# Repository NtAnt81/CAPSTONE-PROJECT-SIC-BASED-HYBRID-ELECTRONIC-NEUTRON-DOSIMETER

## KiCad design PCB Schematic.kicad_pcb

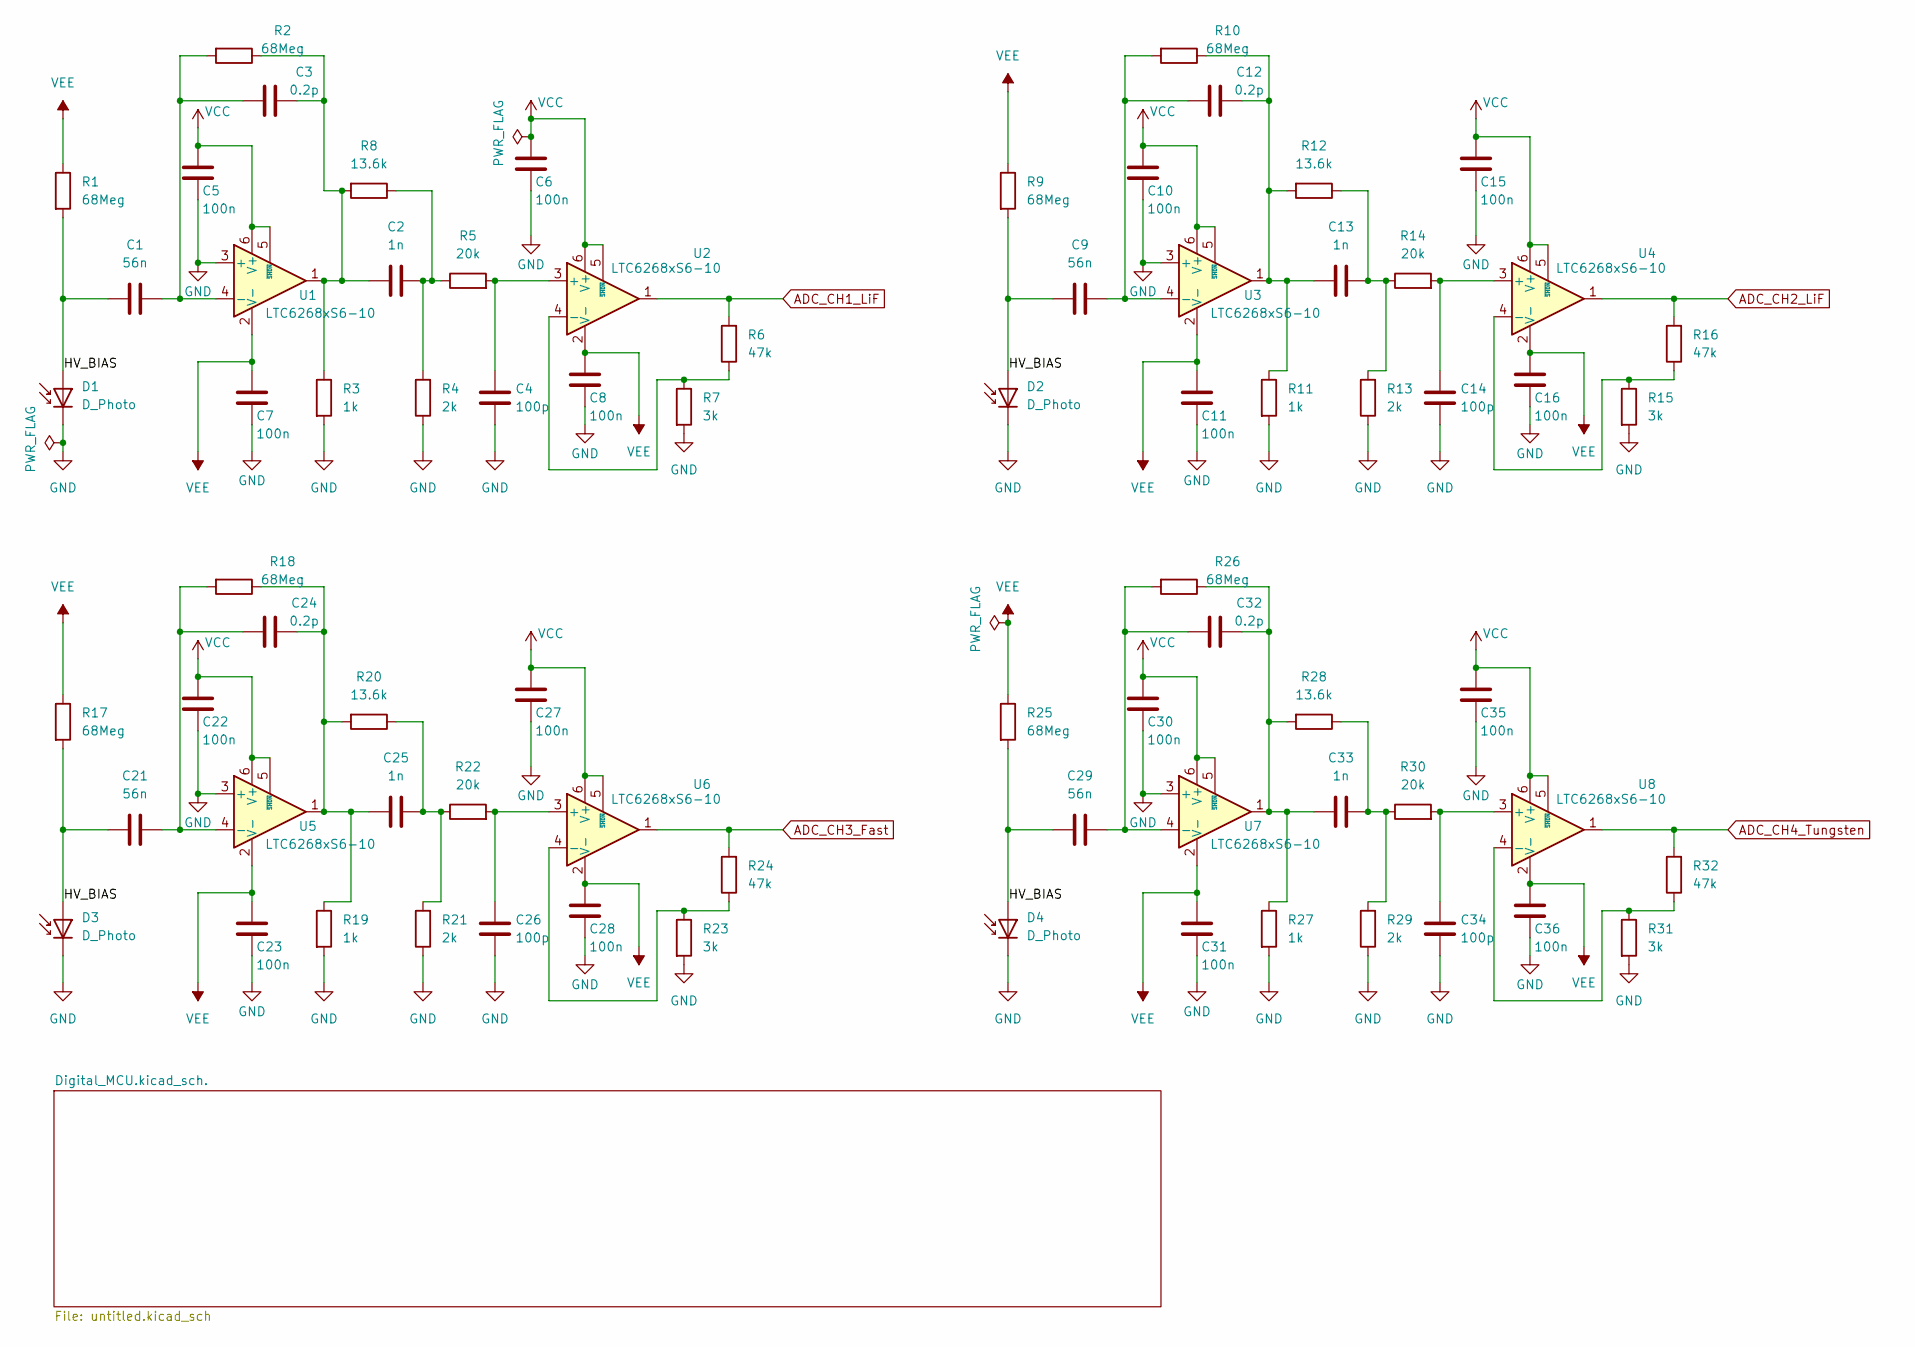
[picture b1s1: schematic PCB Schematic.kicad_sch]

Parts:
C1, C9, C21, C29: 56n; C_0603_1608Metric
C2, C13, C25, C33: 1n; C_0603_1608Metric
C3, C12, C24, C32: 0.2p; C_0603_1608Metric
C4, C14, C26, C34: 100p; C_0603_1608Metric
C5, C6, C7, C8, C10, C11, C15, C16, C22, C23, C27, C28, C30, C31, C35, C36: 100n; C_0201_0603Metric
D1, D2, D3, D4: D_Photo; SiC_Detector_10mm_Die
R1, R2, R9, R10, R17, R18, R25, R26: 68Meg; R_0603_1608Metric
R3, R11, R19, R27: 1k; R_0603_1608Metric
R4, R13, R21, R29: 2k; R_0603_1608Metric
R5, R14, R22, R30: 20k; R_0603_1608Metric
R6, R16, R24, R32: 47k; R_0603_1608Metric
R7, R15, R23, R31: 3k; R_0603_1608Metric
R8, R12, R20, R28: 13.6k; R_0603_1608Metric
U1, U3, U5, U7: LTC6268xS6-10; SOT-23-6
U2, U4, U6, U8: LTC6268xS6-10; TSOT-23-6

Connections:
/HV_BIAS: C1.1, C9.1, C21.1, C29.1, D1.2 (A), D2.2 (A), D3.2 (A), D4.2 (A), R1.2, R9.2, R17.2, R25.2
ADC_CH1_LiF: R6.2, U2.1; also elsewhere on the board
ADC_CH2_LiF: R16.2, U4.1; also elsewhere on the board
ADC_CH3_Fast: R24.2, U6.1; also elsewhere on the board
ADC_CH4_Tungsten: R32.2, U8.1; also elsewhere on the board
GND: C4.1, C5.1, C6.1, C7.1, C8.1, C10.1, C11.1, C14.1, C15.1, C16.1, C22.1, C23.1, C26.1, C27.1, C28.1, C30.1, C31.1, C34.1, C35.1, C36.1, D1.1 (K), D2.1 (K), D3.1 (K), D4.1 (K), R3.2, R4.1, R7.2, R11.2, R13.1, R15.2, R19.2, R21.1, R23.2, R27.2, R29.1, R31.2, U1.3 (+), U3.3 (+), U5.3 (+), U7.3 (+); also elsewhere on the board
unnamed: C2.1, C3.1, R2.1, R3.1, R8.2, U1.1
unnamed: C2.2, R4.2, R5.1, R8.1
unnamed: C12.1, C13.1, R10.1, R11.1, R12.2, U3.1
unnamed: C13.2, R12.1, R13.2, R14.1
unnamed: C24.1, C25.1, R18.1, R19.1, R20.2, U5.1
unnamed: C25.2, R20.1, R21.2, R22.1
unnamed: C32.1, C33.1, R26.1, R27.1, R28.2, U7.1
unnamed: C33.2, R28.1, R29.2, R30.1
unnamed: C1.2, C3.2, R2.2, U1.4 (-)
unnamed: C4.2, R5.2, U2.3 (+)
unnamed: R6.1, R7.1, U2.4 (-)
unnamed: C9.2, C12.2, R10.2, U3.4 (-)
unnamed: C14.2, R14.2, U4.3 (+)
unnamed: R15.1, R16.1, U4.4 (-)
unnamed: C21.2, C24.2, R18.2, U5.4 (-)
unnamed: C26.2, R22.2, U6.3 (+)
unnamed: R23.1, R24.1, U6.4 (-)
unnamed: C29.2, C32.2, R26.2, U7.4 (-)
unnamed: C34.2, R30.2, U8.3 (+)
unnamed: R31.1, R32.1, U8.4 (-)
VCC: C5.2, C6.2, C10.2, C15.2, C22.2, C27.2, C30.2, C35.2, U1.5 (~SHDN), U1.6 (V+), U2.5 (~SHDN), U2.6 (V+), U3.5 (~SHDN), U3.6 (V+), U4.5 (~SHDN), U4.6 (V+), U5.5 (~SHDN), U5.6 (V+), U6.5 (~SHDN), U6.6 (V+), U7.5 (~SHDN), U7.6 (V+), U8.5 (~SHDN), U8.6 (V+)
VEE: C7.2, C8.2, C11.2, C16.2, C23.2, C28.2, C31.2, C36.2, R1.1, R9.1, R17.1, R25.1, U1.2 (V-), U2.2 (V-), U3.2 (V-), U4.2 (V-), U5.2 (V-), U6.2 (V-), U7.2 (V-), U8.2 (V-)

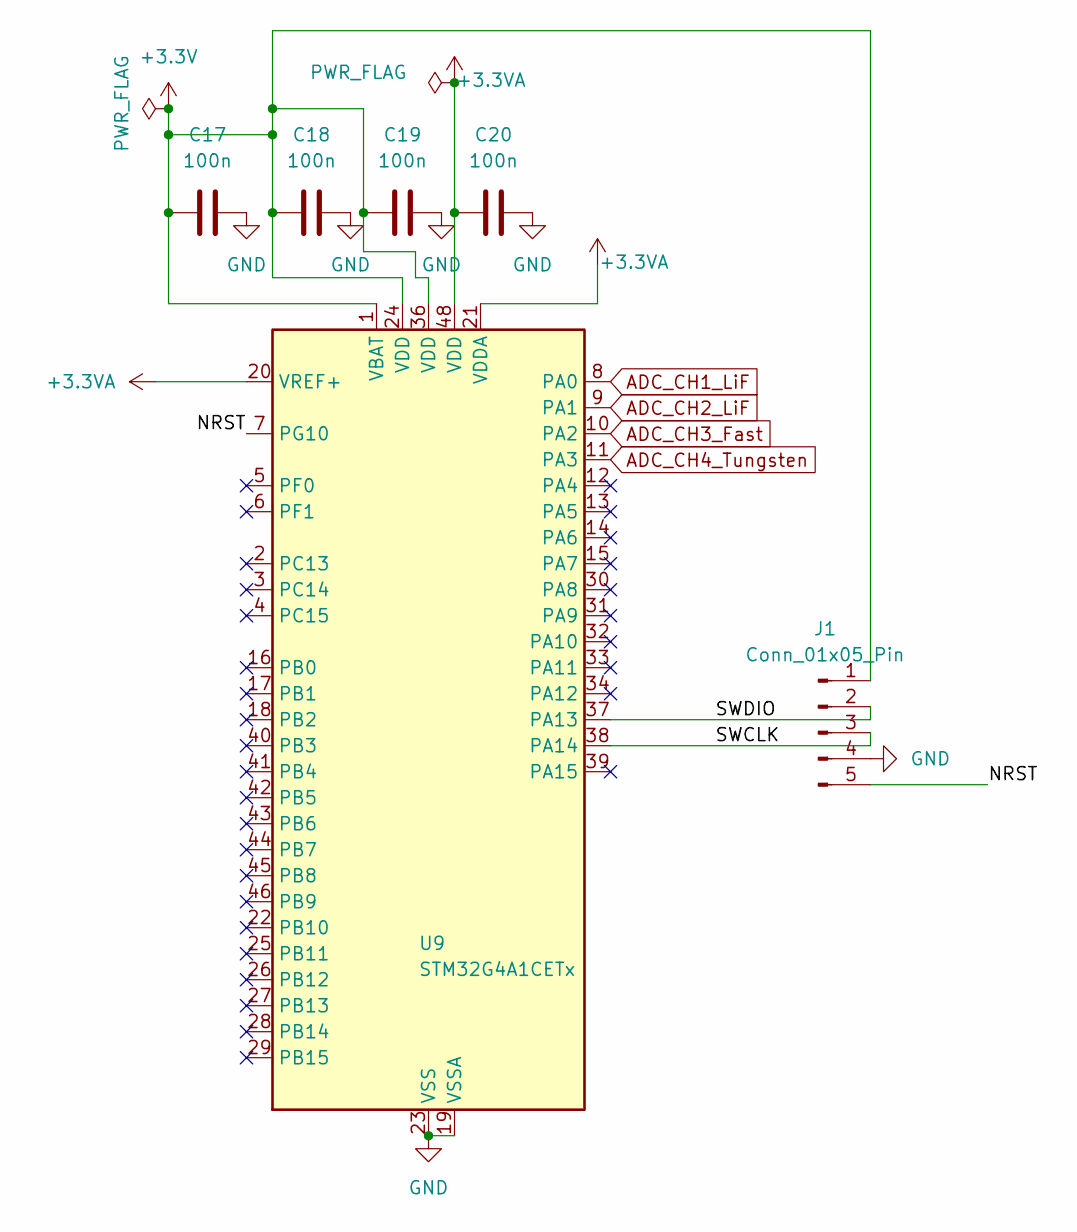
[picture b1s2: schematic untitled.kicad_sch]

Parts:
C17, C18, C19, C20: 100n; C_0603_1608Metric
J1: Conn_01x05_Pin; PinHeader_1x05_P2.54mm_Vertical
U9: STM32G4A1CETx; LQFP-48_7x7mm_P0.5mm

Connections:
+3.3V: C17.2, C18.2, C19.2, J1.1, U9.1 (VBAT), U9.24 (VDD), U9.36 (VDD)
+3.3VA: C20.2, U9.20 (VREF+), U9.21 (VDDA), U9.48 (VDD)
/Digital_MCU.kicad_sch./NRST: J1.5, U9.7 (PG10)
/Digital_MCU.kicad_sch./SWCLK: J1.3, U9.38 (PA14)
/Digital_MCU.kicad_sch./SWDIO: J1.2, U9.37 (PA13)
ADC_CH1_LiF: U9.8 (PA0); also elsewhere on the board
ADC_CH2_LiF: U9.9 (PA1); also elsewhere on the board
ADC_CH3_Fast: U9.10 (PA2); also elsewhere on the board
ADC_CH4_Tungsten: U9.11 (PA3); also elsewhere on the board
GND: C17.1, C18.1, C19.1, C20.1, J1.4, U9.19 (VSSA), U9.23 (VSS), U9.35 (VSS), U9.47 (VSS); also elsewhere on the board

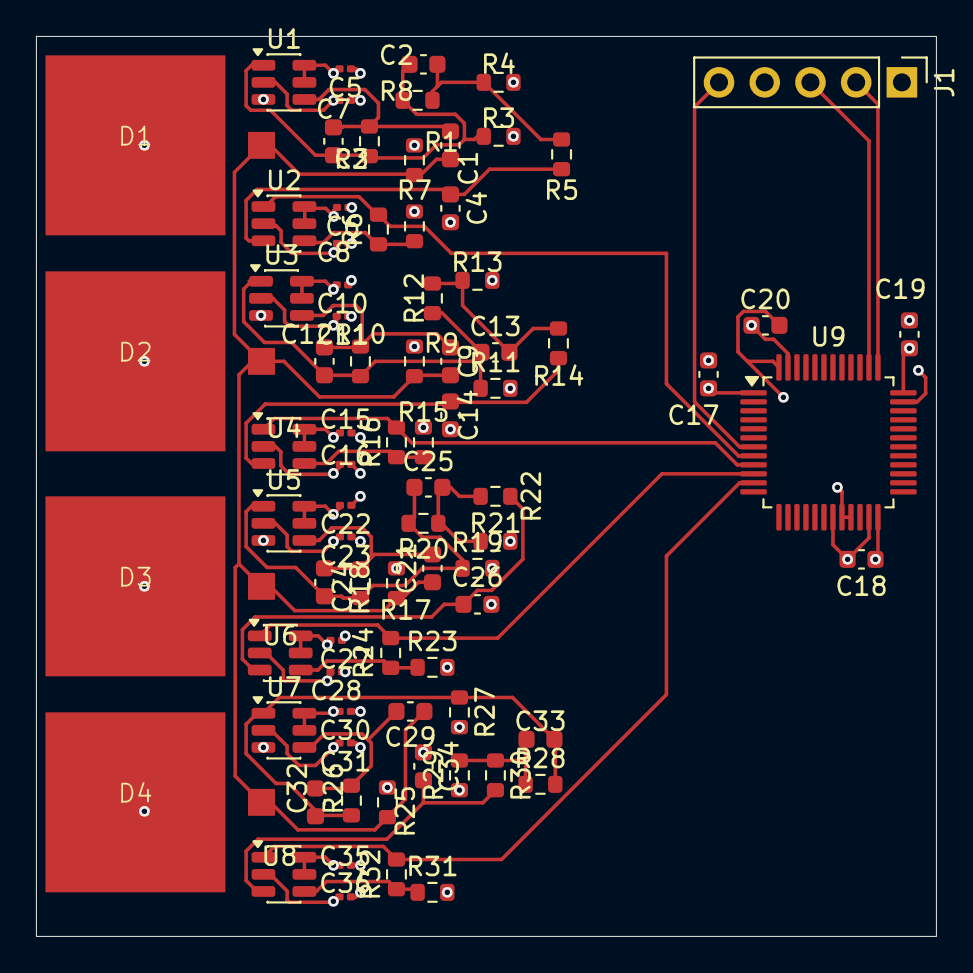
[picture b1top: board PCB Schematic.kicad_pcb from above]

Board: 4 copper layers, 50.0 x 50.0 mm, 82 parts (0 on the bottom side), 33 nets.
